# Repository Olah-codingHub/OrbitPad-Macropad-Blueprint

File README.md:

# OrbitPad-Macropad-Blueprint
A custom 16-key macro-pad built with Seeed Studio XIAO .

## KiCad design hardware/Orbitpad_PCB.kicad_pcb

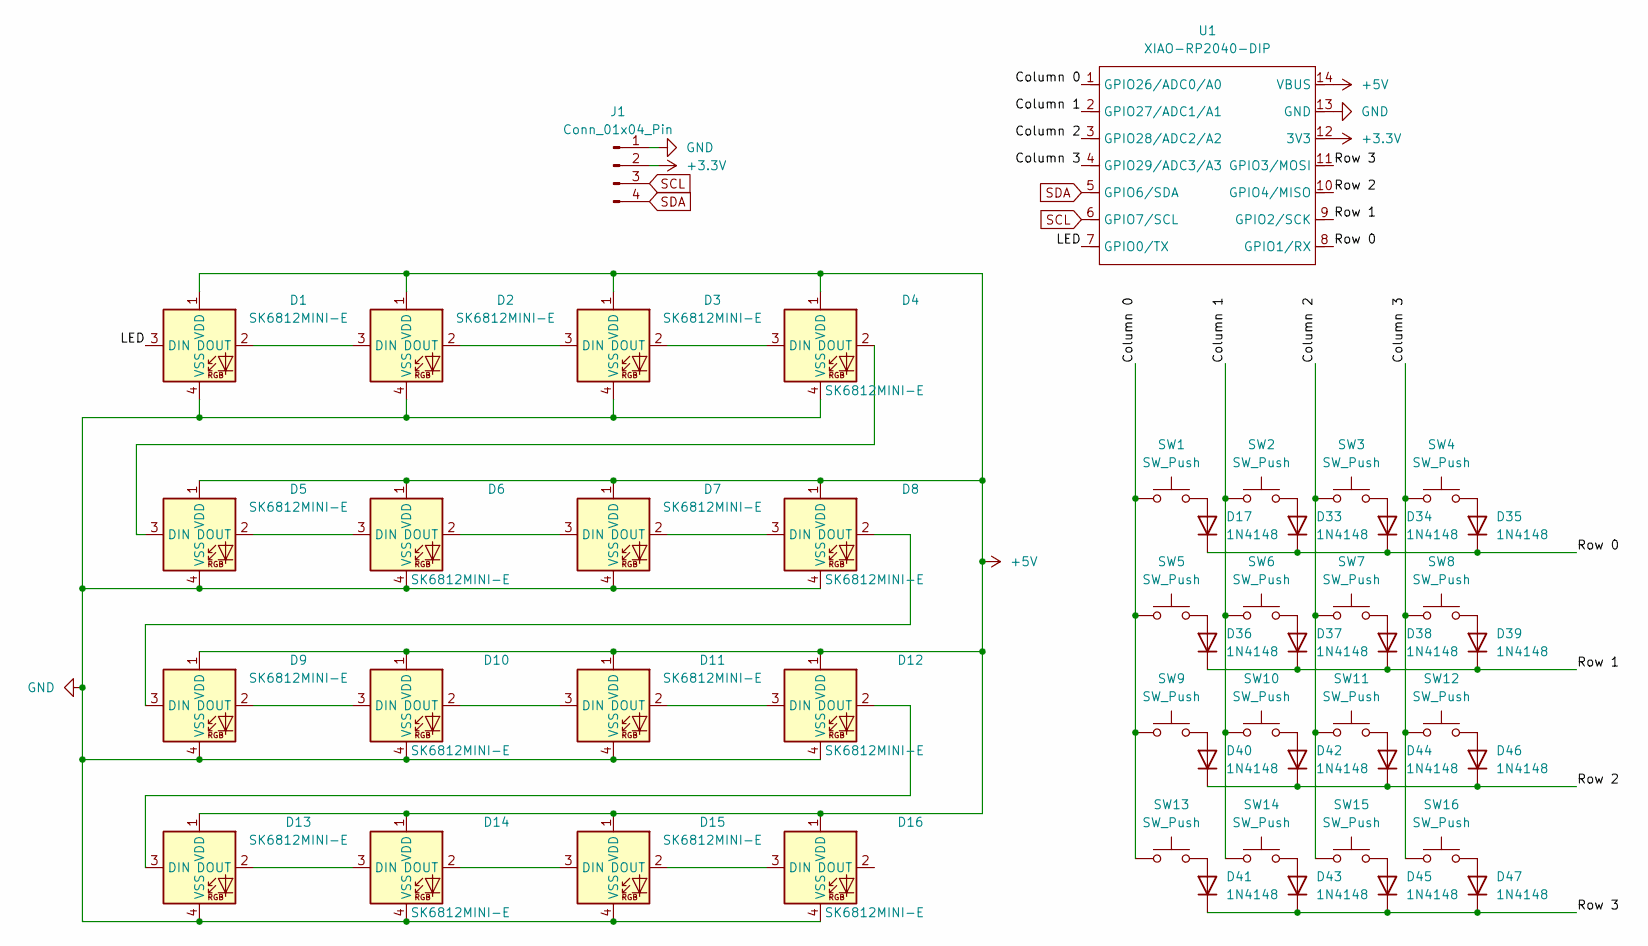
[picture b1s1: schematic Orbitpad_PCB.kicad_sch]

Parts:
D1, D2, D3, D4, D5, D6, D7, D8, D9, D10, D11, D12, D13, D14, D15, D16: SK6812MINI-E; LED_6028R
D17, D33, D34, D35, D36, D37, D38, D39, D40, D41, D42, D43, D44, D45, D46, D47: 1N4148; D_DO-35_SOD27_P7.62mm_Horizontal
J1: Conn_01x04_Pin; PinHeader_1x04_P2.54mm_Vertical
SW1, SW2, SW3, SW4, SW5, SW6, SW7, SW8, SW9, SW10, SW11, SW12, SW13, SW14, SW15, SW16: SW_Push; SW_Cherry_MX_1.00u_PCB
U1: XIAO-RP2040-DIP

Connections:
+3.3V: J1.2, U1.12 (3V3)
+5V: D1.1 (VDD), D2.1 (VDD), D3.1 (VDD), D4.1 (VDD), D5.1 (VDD), D6.1 (VDD), D7.1 (VDD), D8.1 (VDD), D9.1 (VDD), D10.1 (VDD), D11.1 (VDD), D12.1 (VDD), D13.1 (VDD), D14.1 (VDD), D15.1 (VDD), D16.1 (VDD), U1.14 (VBUS)
/Column 0: SW1.1, SW5.1, SW9.1, SW13.1, U1.1 (GPIO26/ADC0/A0)
/Column 1: SW2.1, SW6.1, SW10.1, SW14.1, U1.2 (GPIO27/ADC1/A1)
/Column 2: SW3.1, SW7.1, SW11.1, SW15.1, U1.3 (GPIO28/ADC2/A2)
/Column 3: SW4.1, SW8.1, SW12.1, SW16.1, U1.4 (GPIO29/ADC3/A3)
/LED: D1.3 (DIN), U1.7 (GPIO0/TX)
/Row 0: D17.1 (K), D33.1 (K), D34.1 (K), D35.1 (K), U1.8 (GPIO1/RX)
/Row 1: D36.1 (K), D37.1 (K), D38.1 (K), D39.1 (K), U1.9 (GPIO2/SCK)
/Row 2: D40.1 (K), D42.1 (K), D44.1 (K), D46.1 (K), U1.10 (GPIO4/MISO)
/Row 3: D41.1 (K), D43.1 (K), D45.1 (K), D47.1 (K), U1.11 (GPIO3/MOSI)
GND: D1.4 (VSS), D2.4 (VSS), D3.4 (VSS), D4.4 (VSS), D5.4 (VSS), D6.4 (VSS), D7.4 (VSS), D8.4 (VSS), D9.4 (VSS), D10.4 (VSS), D11.4 (VSS), D12.4 (VSS), D13.4 (VSS), D14.4 (VSS), D15.4 (VSS), D16.4 (VSS), J1.1, U1.13 (GND)
unnamed: D1.2 (DOUT), D2.3 (DIN)
unnamed: D2.2 (DOUT), D3.3 (DIN)
unnamed: D3.2 (DOUT), D4.3 (DIN)
unnamed: D4.2 (DOUT), D5.3 (DIN)
unnamed: D5.2 (DOUT), D6.3 (DIN)
unnamed: D6.2 (DOUT), D7.3 (DIN)
unnamed: D7.2 (DOUT), D8.3 (DIN)
unnamed: D8.2 (DOUT), D9.3 (DIN)
unnamed: D10.2 (DOUT), D11.3 (DIN)
unnamed: D9.2 (DOUT), D10.3 (DIN)
unnamed: D11.2 (DOUT), D12.3 (DIN)
unnamed: D12.2 (DOUT), D13.3 (DIN)
unnamed: D13.2 (DOUT), D14.3 (DIN)
unnamed: D14.2 (DOUT), D15.3 (DIN)
unnamed: D15.2 (DOUT), D16.3 (DIN)
unnamed: D17.2 (A), SW1.2
unnamed: D33.2 (A), SW2.2
unnamed: D34.2 (A), SW3.2
unnamed: D35.2 (A), SW4.2
unnamed: D36.2 (A), SW5.2
unnamed: D37.2 (A), SW6.2
unnamed: D38.2 (A), SW7.2
unnamed: D39.2 (A), SW8.2
unnamed: D40.2 (A), SW9.2
unnamed: D41.2 (A), SW13.2
unnamed: D42.2 (A), SW10.2
unnamed: D43.2 (A), SW14.2
unnamed: D44.2 (A), SW11.2
unnamed: D45.2 (A), SW15.2
unnamed: D46.2 (A), SW12.2
unnamed: D47.2 (A), SW16.2
SCL: J1.3, U1.6 (GPIO7/SCL)
SDA: J1.4, U1.5 (GPIO6/SDA)

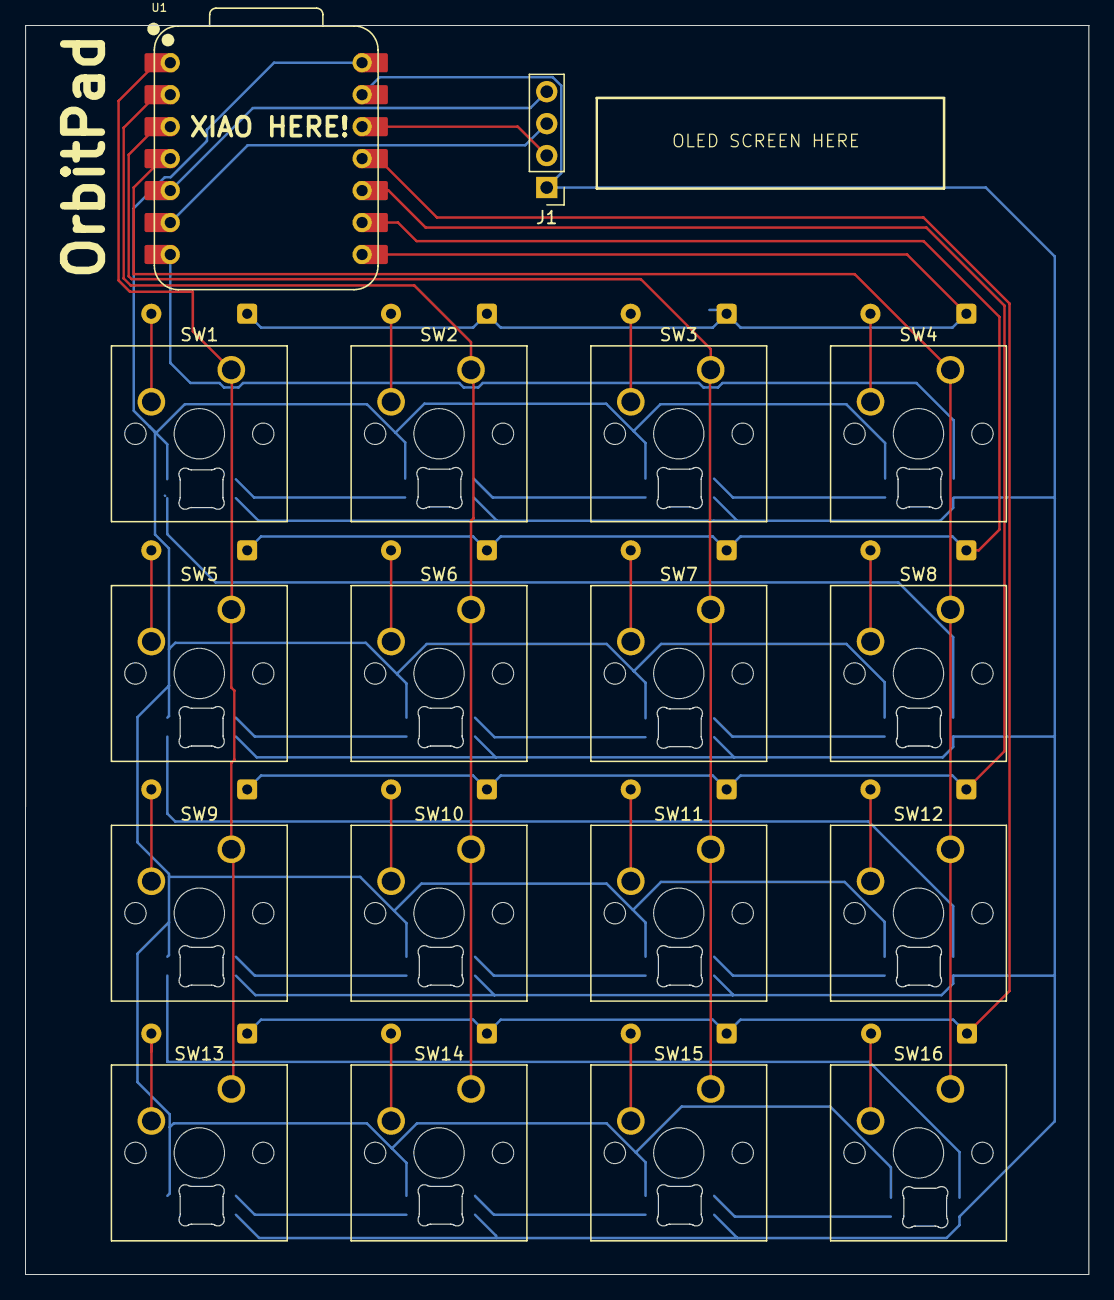
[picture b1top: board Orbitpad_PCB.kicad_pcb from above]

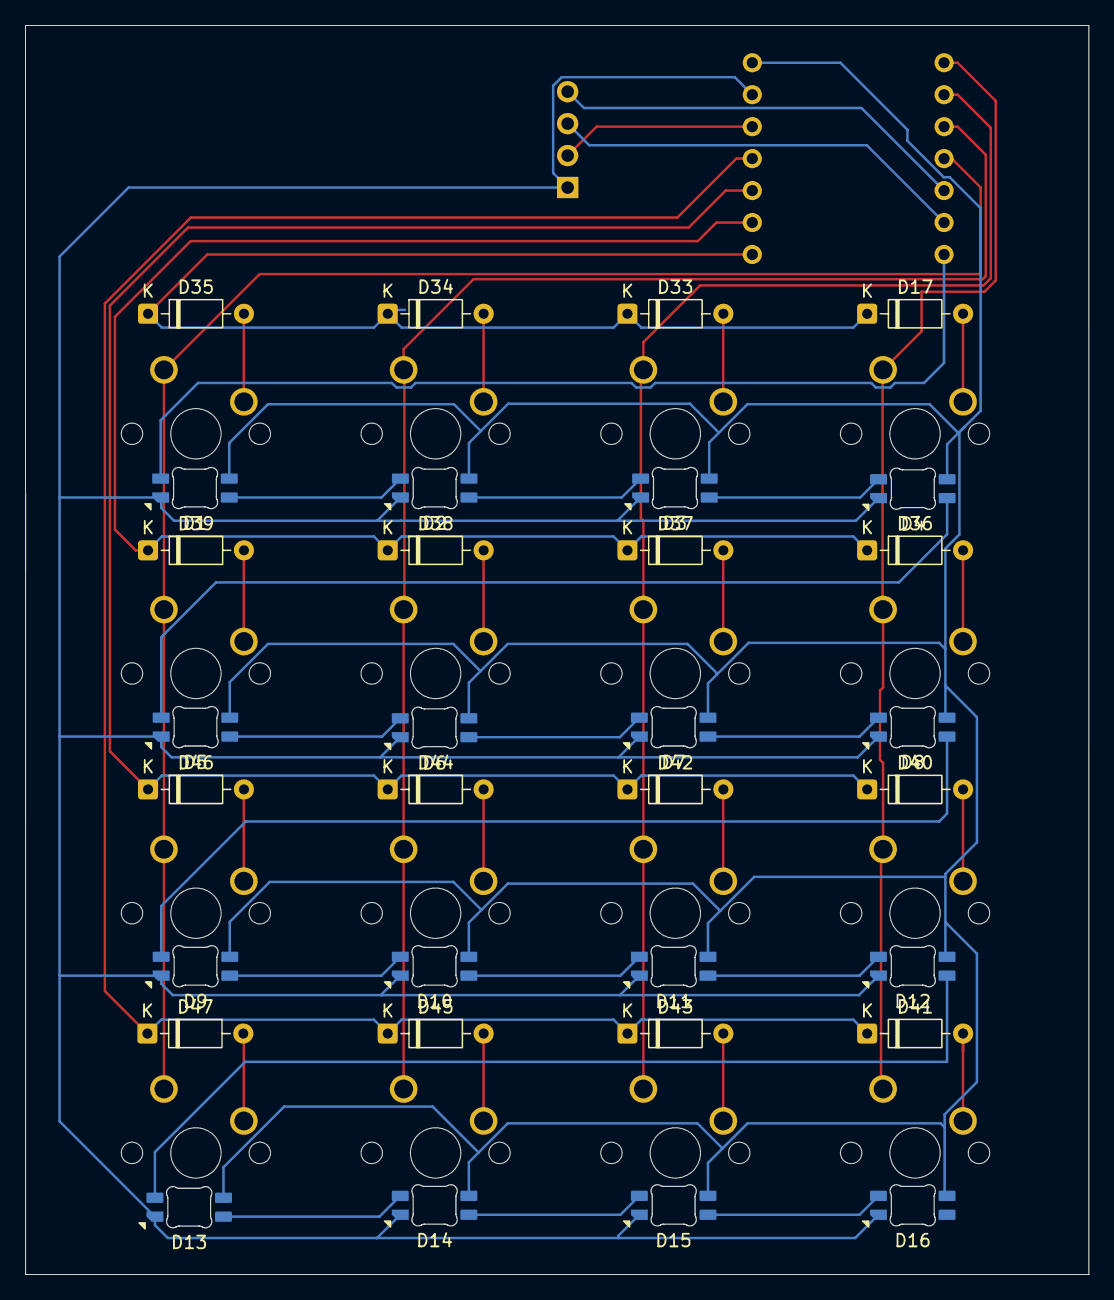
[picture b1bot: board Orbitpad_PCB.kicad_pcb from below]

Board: 2 copper layers, 84.5 x 99.3 mm, 50 parts (32 on the bottom side), 45 nets.
